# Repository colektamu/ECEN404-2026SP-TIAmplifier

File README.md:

The 2025-2026 TI Amplifier Capstone Project was a senior year capstone project under Texas A&M University and sponsored by Texas Instruments. The project was completed by Haotian Guan, Cole Keating, Braeden Murdock, and Jonathan Roman under the mentorship and supervision of Alex Anderson as a contact with Texas Instruments. The files included in this GitHub repository reflect the progress updates and final version of the project.

Each folder within the repository reflects a single subsystem that contributed to the final project. 
Braeden Murdock integrated pcb power subsystem contains files relevant to the power subsystem that powered the device. 
Cole - Pre and power amp contains the files relevant to the analog subsystem, both the preamp that modulated the signal and the power amp that amplified it into the speaker output. 
Microcontroller - Jonathan Roman contains the pcb and code files for the microcontroller subsystem, used to translate mobile app inputs into potentiometer states on the audio circuits.

All other files found in the repository without a set folder are related documentation such as the Functional System Requirements and Validation Plan.

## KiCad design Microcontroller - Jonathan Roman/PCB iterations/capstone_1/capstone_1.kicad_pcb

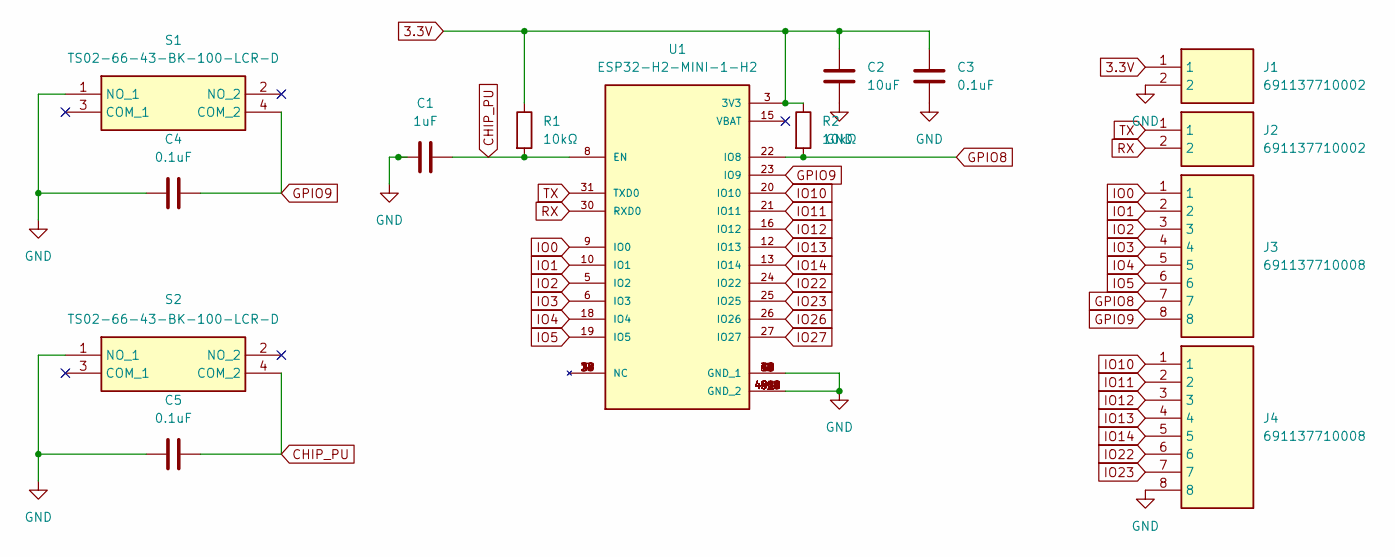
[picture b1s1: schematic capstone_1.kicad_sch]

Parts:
C1: 1uF; C_1206_3216Metric
C2: 10uF; C_1206_3216Metric
C3, C4, C5: 0.1uF; C_1206_3216Metric
J1, J2: 691137710002; SHDR2W70P0X500_1X2_1000X750X1160P; Mouser Part Number 710-691137710002
J3, J4: 691137710008; Mouser Part Number 710-691137710008
R1, R2: 10kΩ; R_1206_3216Metric
S1, S2: TS02-66-43-BK-100-LCR-D; TS026643BK100LCRD; Mouser Part Number 179-TS026643BK100LCR
U1: ESP32-H2-MINI-1-H2; MODULE_ESP32-H2-MINI-1-H2; PARTREV v0.5

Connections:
3.3V: C2.1, C3.1, J1.1, R1.1, R2.1, U1.3 (3V3)
CHIP_PU: C1.1, C5.2, R1.2, S2.4 (COM_2), U1.8 (EN)
GND: C1.2, C2.2, C3.2, C4.1, C5.1, J1.2, J4.8, S1.1 (NO_1), S2.1 (NO_1), U1.1 (GND_1), U1.2 (GND_1), U1.11 (GND_1), U1.14 (GND_1), U1.36 (GND_1), U1.37 (GND_1), U1.38 (GND_1), U1.39 (GND_1), U1.40 (GND_1), U1.41 (GND_1), U1.42 (GND_1), U1.43 (GND_1), U1.44 (GND_1), U1.45 (GND_1), U1.46 (GND_1), U1.47 (GND_2), U1.48 (GND_2), U1.49_1 (GND_2), U1.49_2 (GND_2), U1.49_3 (GND_2), U1.49_4 (GND_2), U1.49_5 (GND_2), U1.49_6 (GND_2), U1.49_7 (GND_2), U1.49_8 (GND_2), U1.49_9 (GND_2), U1.50 (GND_2), U1.51 (GND_2), U1.52 (GND_2), U1.53 (GND_2)
GPIO8: J3.7, R2.2, U1.22 (IO8)
GPIO9: C4.2, J3.8, S1.4 (COM_2), U1.23 (IO9)
IO0: J3.1, U1.9 (IO0)
IO1: J3.2, U1.10 (IO1)
IO2: J3.3, U1.5 (IO2)
IO3: J3.4, U1.6 (IO3)
IO4: J3.5, U1.18 (IO4)
IO5: J3.6, U1.19 (IO5)
IO10: J4.1, U1.20 (IO10)
IO11: J4.2, U1.21 (IO11)
IO12: J4.3, U1.16 (IO12)
IO13: J4.4, U1.12 (IO13)
IO14: J4.5, U1.13 (IO14)
IO22: J4.6, U1.24 (IO22)
IO23: J4.7, U1.25 (IO25)
IO26: U1.26 (IO26)
IO27: U1.27 (IO27)
RX: J2.2, U1.30 (RXD0)
TX: J2.1, U1.31 (TXD0)

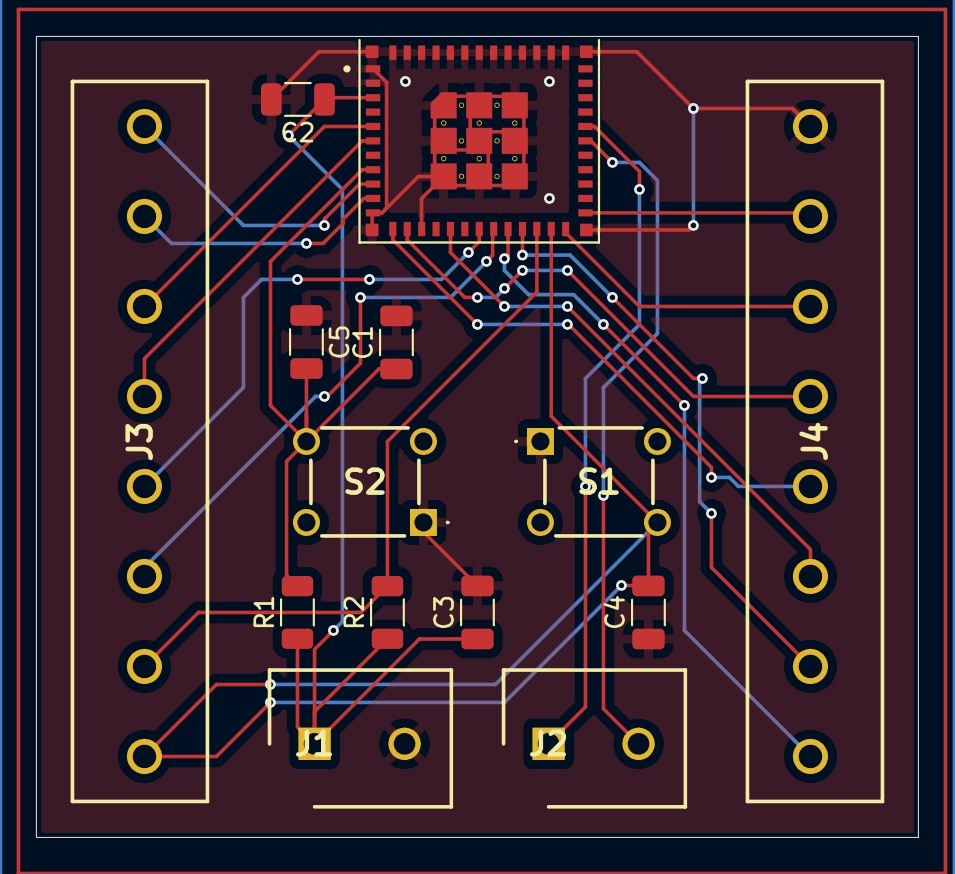
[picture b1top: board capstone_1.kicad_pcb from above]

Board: 2 copper layers, 49.0 x 44.5 mm, 14 parts (0 on the bottom side), 20 nets.

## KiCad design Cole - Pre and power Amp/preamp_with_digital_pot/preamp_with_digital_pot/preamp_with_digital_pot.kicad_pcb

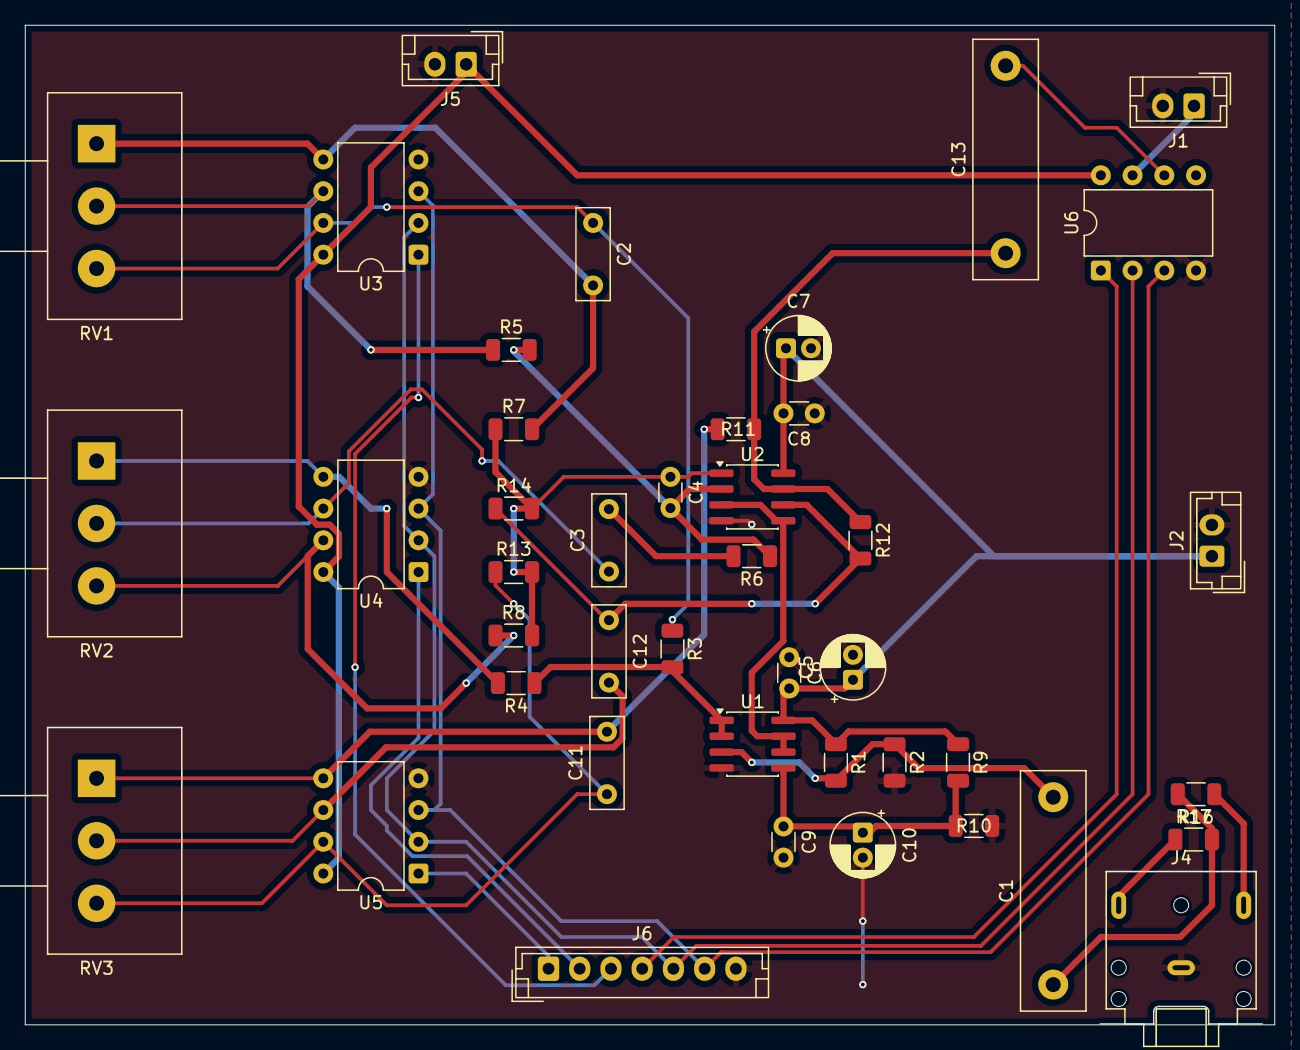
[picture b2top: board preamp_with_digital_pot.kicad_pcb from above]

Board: 2 copper layers, 99.9 x 79.9 mm, 43 parts (0 on the bottom side), 32 nets.

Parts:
C1, C13: 2.2μF; C_Rect_L19.0mm_W5.0mm_P15.00mm_MKS4
C2: 100nF; C_Rect_L7.2mm_W2.5mm_P5.00mm_FKS2_FKP2_MKS2_MKP2
C3: 2.2nF; C_Rect_L7.2mm_W2.5mm_P5.00mm_FKS2_FKP2_MKS2_MKP2
C4: 22pF; C_Disc_D3.0mm_W1.6mm_P2.50mm
C5, C7, C10: 10μF; CP_Radial_D5.0mm_P2.00mm
C6, C8, C9: 0.1μF; C_Disc_D3.0mm_W1.6mm_P2.50mm
C11: 15nF; C_Rect_L7.2mm_W2.5mm_P5.00mm_FKS2_FKP2_MKS2_MKP2
C12: 22nF; C_Rect_L7.2mm_W2.5mm_P5.00mm_FKS2_FKP2_MKS2_MKP2
J1, J2, J5: Conn_01x02; JST_EH_B2B-EH-A_1x02_P2.50mm_Vertical
J4: AudioJack3; Jack_3.5mm_CUI_SJ1-3523N_Horizontal
J6: Conn_01x07; JST_EH_B7B-EH-A_1x07_P2.50mm_Vertical
R1, R2: 100k; R_1206_3216Metric
R3, R7: 5k; R_1206_3216Metric
R4, R8: 2.8k; R_1206_3216Metric
R5: 22k; R_1206_3216Metric
R6: 4.7k; R_1206_3216Metric
R9, R10, R12, R14: 47k; R_1206_3216Metric
R11, R13: 3.6k; R_1206_3216Metric
R16, R17: 2.2k; R_1206_3216Metric
RV1, RV2, RV3: R_Potentiometer; Potentiometer_Alps_RK163_Single_Horizontal
U1, U2: OPA1656ID; SOIC-8_3.9x4.9mm_P1.27mm
U3, U4, U5, U6: MCP4131-xxxx-P; DIP-8_W7.62mm

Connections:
+3.3V: J5.1, U3.8 (V_{DD}), U4.8 (V_{DD}), U5.8 (V_{DD}), U6.8 (V_{DD})
+6V: U1.6 (-), U1.7, U2.3 (+), U2.5 (+)
+12V: C5.1, C6.2, C7.1, C8.2, J2.1, R1.1, R9.1, U1.8 (V+), U2.8 (V+)
CS_BASS: J6.3, U3.1 (~CS)
CS_MID: J6.1, U5.1 (~CS)
CS_TREBLE: J6.2, U4.1 (~CS)
GND: C5.2, C6.1, C7.2, C8.1, C9.2, C10.2, J1.2, J2.2, J4.S, J5.2, J6.7, R2.2, R10.2, U1.4 (V-), U2.4 (V-), U3.4 (V_{SS}), U4.4 (V_{SS}), U5.4 (V_{SS}), U6.4 (V_{SS})
unnamed: C1.1, R16.2, R17.2
unnamed: C3.2, R6.2
unnamed: C4.1, R7.1, R8.2, R13.2, R14.2, U2.1
unnamed: C13.1, R11.2, R12.1, U2.7
unnamed: J1.1, U6.7 (P0B)
unnamed: J4.R, R17.1
unnamed: J4.T, R16.1
unnamed: C1.2, R1.2, R2.1, U1.3 (+)
unnamed: R3.2, R4.1, U1.1, U1.2 (-)
unnamed: C9.1, C10.1, R9.2, R10.1, U1.5 (+)
unnamed: C4.2, R5.2, R6.1, U2.2 (-)
unnamed: C12.1, R12.2, R14.1, U2.6 (-)
unnamed: C2.2, R7.2, RV1.1, U3.5 (P0A)
unnamed: C2.1, R3.1, RV1.3, U3.7 (P0B)
unnamed: R5.1, RV1.2, U3.6 (P0W)
unnamed: R4.2, RV2.1, U4.5 (P0A)
unnamed: R8.1, RV2.3, U4.7 (P0B)
unnamed: C3.1, RV2.2, U4.6 (P0W)
unnamed: C11.2, R11.1, RV3.1, U5.5 (P0A)
unnamed: C11.1, R13.1, RV3.3, U5.7 (P0B)
unnamed: C12.2, RV3.2, U5.6 (P0W)
unnamed: C13.2, U6.6 (P0W)
SCK: J6.5, U3.2 (SCK), U4.2 (SCK), U5.2 (SCK), U6.2 (SCK)
SDI: J6.6, U3.3 (SDI/SDO), U4.3 (SDI/SDO), U5.3 (SDI/SDO), U6.3 (SDI/SDO)
VOL: J6.4, U6.1 (~CS)

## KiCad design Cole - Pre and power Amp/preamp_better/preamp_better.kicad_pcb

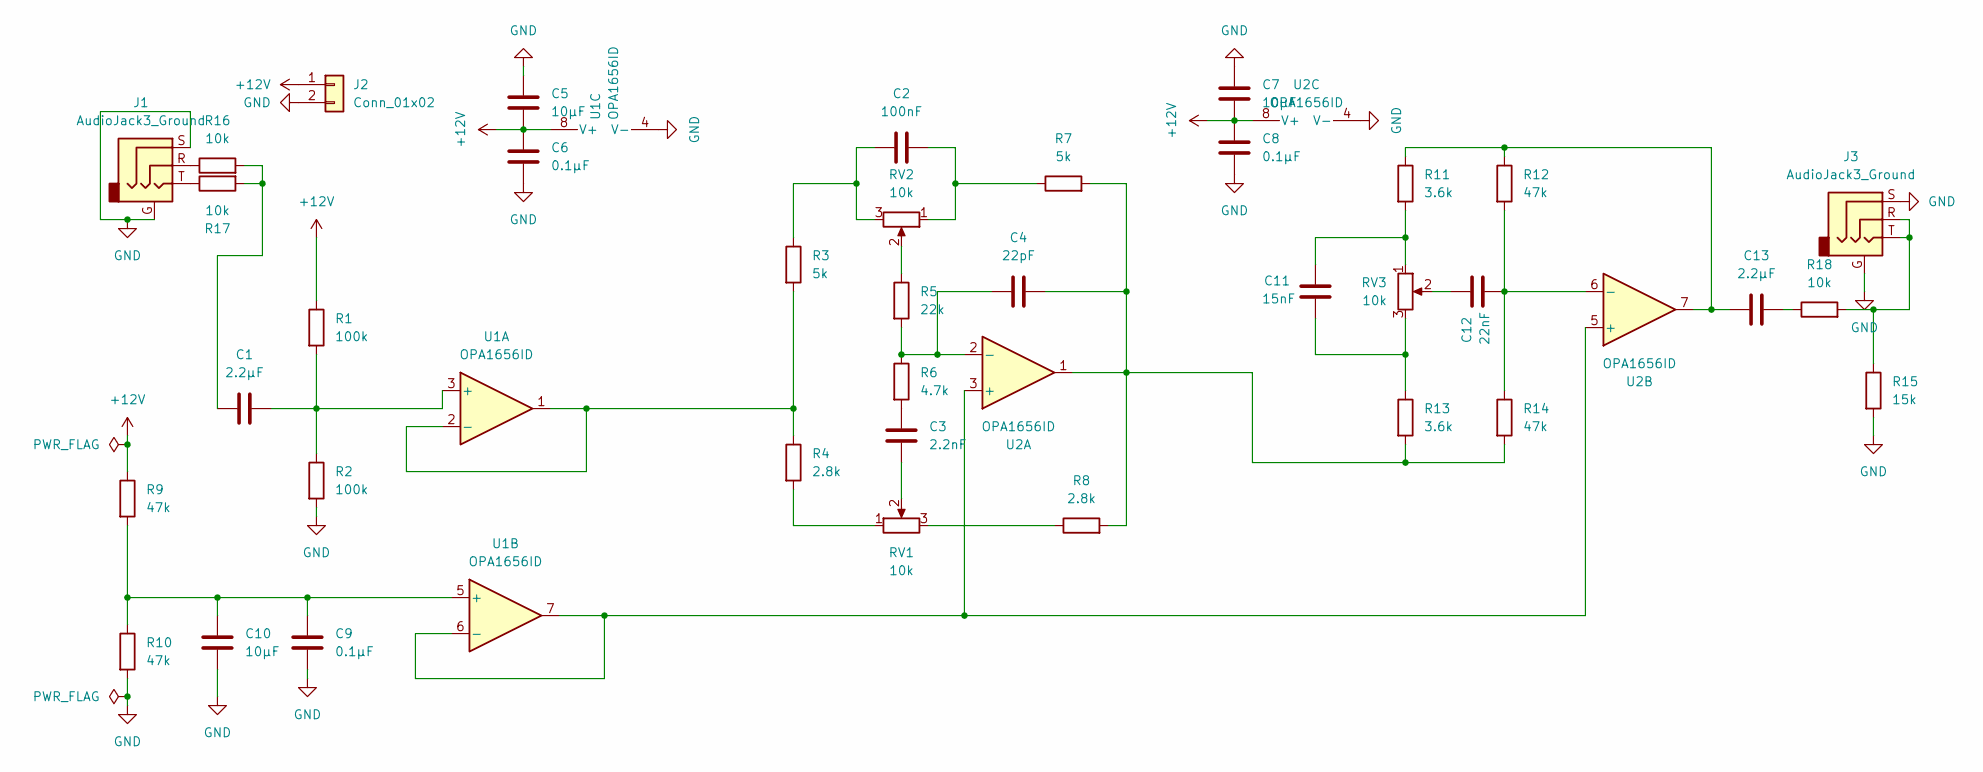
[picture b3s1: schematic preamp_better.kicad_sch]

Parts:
C1, C13: 2.2μF; C_Rect_L19.0mm_W5.0mm_P15.00mm_MKS4
C2: 100nF; C_Rect_L7.2mm_W2.5mm_P5.00mm_FKS2_FKP2_MKS2_MKP2
C3: 2.2nF; C_Rect_L7.2mm_W2.5mm_P5.00mm_FKS2_FKP2_MKS2_MKP2
C4: 22pF; C_Disc_D3.0mm_W1.6mm_P2.50mm
C5, C7, C10: 10μF; CP_Radial_D5.0mm_P2.00mm
C6, C8, C9: 0.1μF; C_Disc_D3.0mm_W1.6mm_P2.50mm
C11: 15nF; C_Rect_L7.2mm_W2.5mm_P5.00mm_FKS2_FKP2_MKS2_MKP2
C12: 22nF; C_Rect_L7.2mm_W2.5mm_P5.00mm_FKS2_FKP2_MKS2_MKP2
J1, J3: AudioJack3_Ground; Jack_3.5mm_CUI_SJ1-3523N_Horizontal
J2: Conn_01x02; 691137710002
R1, R2: 100k; R_1206_3216Metric
R3, R7: 5k; R_1206_3216Metric
R4, R8: 2.8k; R_1206_3216Metric
R5: 22k; R_1206_3216Metric
R6: 4.7k; R_1206_3216Metric
R9, R10, R12, R14: 47k; R_1206_3216Metric
R11, R13: 3.6k; R_1206_3216Metric
R15: 15k; R_1206_3216Metric
R16, R17, R18: 10k; R_1206_3216Metric
RV1, RV2, RV3: 10k; Potentiometer_Alps_RK163_Single_Horizontal
U1, U2: OPA1656ID; SOIC-8_3.9x4.9mm_P1.27mm

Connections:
+12V: C5.1, C6.2, C7.1, C8.2, J2.1, R1.1, R9.1, U1.8 (V+), U2.8 (V+)
GND: C5.2, C6.1, C7.2, C8.1, C9.2, C10.2, J1.G, J1.S, J2.2, J3.G, J3.S, R2.2, R10.2, R15.2, U1.4 (V-), U2.4 (V-)
unnamed: C1.1, R16.2, R17.2
unnamed: C2.1, R3.1, RV2.3
unnamed: C2.2, R7.1, RV2.1
unnamed: C3.1, RV1.2
unnamed: C3.2, R6.2
unnamed: C4.1, R7.2, R8.2, R13.2, R14.2, U2.1
unnamed: C11.1, R13.1, RV3.3
unnamed: C11.2, R11.2, RV3.1
unnamed: C12.2, RV3.2
unnamed: C13.1, R11.1, R12.1, U2.7
unnamed: C13.2, R18.1
unnamed: J1.R, R16.1
unnamed: J1.T, R17.1
unnamed: J3.R, J3.T, R15.1, R18.2
unnamed: R4.2, RV1.1
unnamed: R5.1, RV2.2
unnamed: R8.1, RV1.3
unnamed: C1.2, R1.2, R2.1, U1.3 (+)
unnamed: R3.2, R4.1, U1.1, U1.2 (-)
unnamed: C9.1, C10.1, R9.2, R10.1, U1.5 (+)
unnamed: U1.6 (-), U1.7, U2.3 (+), U2.5 (+)
unnamed: C4.2, R5.2, R6.1, U2.2 (-)
unnamed: C12.1, R12.2, R14.1, U2.6 (-)

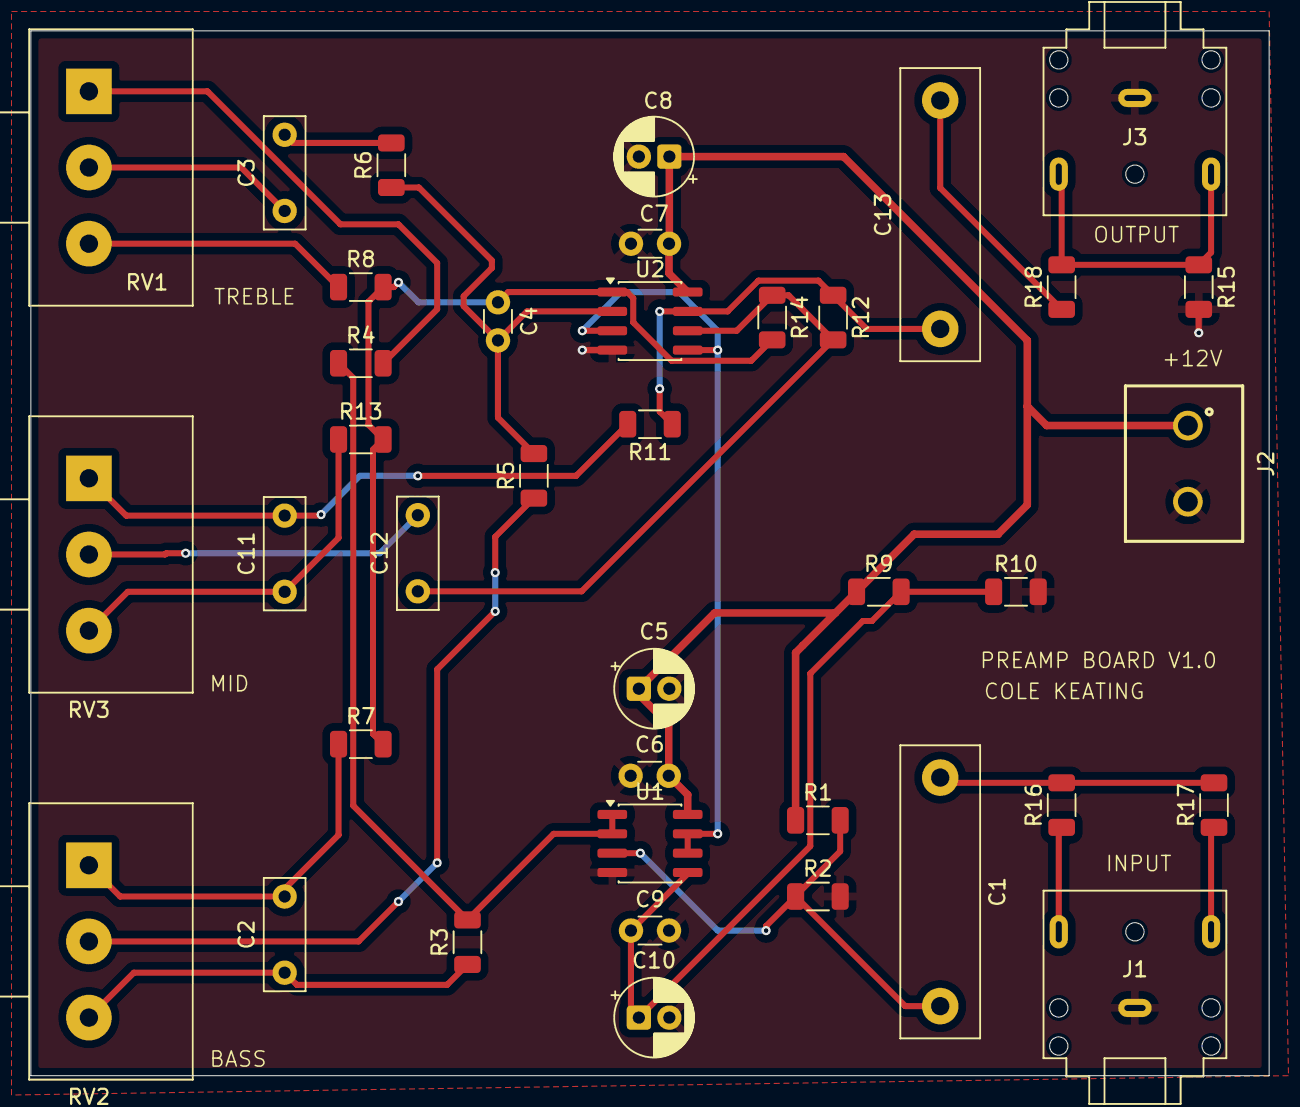
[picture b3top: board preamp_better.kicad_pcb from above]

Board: 2 copper layers, 81.3 x 68.6 mm, 39 parts (0 on the bottom side), 25 nets.

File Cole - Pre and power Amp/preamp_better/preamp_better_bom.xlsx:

Reference | Qty | Value | LINK | Exclude from BOM | Exclude from Board | Footprint | Datasheet
C1,C13 | 2 | 2.2ŒºF |  |  |  | Capacitor_THT:C_Rect_L19.0mm_W5.0mm_P15.00mm_MKS4 | https://www.mouser.com/ProductDetail/871-B32522C225J
C2 | 1 | 100nF |  |  |  | Capacitor_THT:C_Rect_L7.2mm_W2.5mm_P5.00mm_FKS2_FKP2_MKS2_MKP2 | https://www.mouser.com/ProductDetail/Vishay-BC-Components/K1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
C3 | 1 | 2.2nF |  |  |  | Capacitor_THT:C_Rect_L7.2mm_W2.5mm_P5.00mm_FKS2_FKP2_MKS2_MKP2 | https://www.mouser.com/ProductDetail/Vishay-BC-Components/K2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
C4 | 1 | 22pF |  |  |  | Capacitor_THT:C_Disc_D3.0mm_W1.6mm_P2.50mm | https://www.mouser.com/ProductDetail/594-K220J15C0GF5TL2
C5,C7,C10 | 3 | 10ŒºF |  |  |  | Capacitor_THT:CP_Radial_D5.0mm_P2.00mm | https://www.mouser.com/ProductDetail/232-50YXJ10M5X11
C6,C8,C9 | 3 | 0.1ŒºF |  |  |  | Capacitor_THT:C_Disc_D3.0mm_W1.6mm_P2.50mm | https://www.mouser.com/ProductDetail/594-K104K15X7RF5TL2
C11 | 1 | 15nF |  |  |  | Capacitor_THT:C_Rect_L7.2mm_W2.5mm_P5.00mm_FKS2_FKP2_MKS2_MKP2 | https://www.mouser.com/ProductDetail/594-K153K10X7RF5UH5
C12 | 1 | 22nF |  |  |  | Capacitor_THT:C_Rect_L7.2mm_W2.5mm_P5.00mm_FKS2_FKP2_MKS2_MKP2 | https://www.mouser.com/ProductDetail/Vishay-BC-Components/K2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
J1,J3 | 2 | AudioJack3_Ground |  |  |  | Connector_Audio:Jack_3.5mm_CUI_SJ1-3523N_Horizontal | https://www.mouser.com/ProductDetail/490-SJ1-3523N
J2 | 1 | Conn_01x02 |  |  |  | Connector_JST:JST_XH_B2B-XH-A_1x02_P2.50mm_Vertical | https://www.mouser.com/ProductDetail/JST-Commercial/B2B-XH-A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
R1,R2 | 2 | 100k |  |  |  | Resistor_SMD:R_1206_3216Metric | https://www.mouser.com/ProductDetail/603-RC1206FR-07100KL
R3,R7 | 2 | 5k |  |  |  | Resistor_SMD:R_1206_3216Metric | https://www.mouser.com/ProductDetail/603-RC1206FR-074K99L
R4,R8 | 2 | 2.8k |  |  |  | Resistor_SMD:R_1206_3216Metric | https://www.mouser.com/ProductDetail/603-RC1206FR-072K8L
R5 | 1 | 22k |  |  |  | Resistor_SMD:R_1206_3216Metric | https://www.mouser.com/ProductDetail/603-RC1206FR-1022KL
R6 | 1 | 4.7k |  |  |  | Resistor_SMD:R_1206_3216Metric | https://www.mouser.com/ProductDetail/603-RC1206FR-074K7L
R9,R10,R12,R14 | 4 | 47k |  |  |  | Resistor_SMD:R_1206_3216Metric | https://www.mouser.com/ProductDetail/603-RC1206FR-0747KL
R11,R13 | 2 | 3.6k |  |  |  | Resistor_SMD:R_1206_3216Metric | https://www.mouser.com/ProductDetail/YAGEO/RC1206FR-073K6L?q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
R15 | 1 | 15k |  |  |  | Resistor_SMD:R_1206_3216Metric | https://www.mouser.com/ProductDetail/YAGEO/RC1206FR-0715KL?q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
R16,R17,R18 | 3 | 10k |  |  |  | Resistor_SMD:R_1206_3216Metric | https://www.mouser.com/ProductDetail/YAGEO/RC1206FR-0710KL?q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
RV1,RV2,RV3 | 3 | 10k |  |  |  | Potentiometer_THT:Potentiometer_Alps_RK163_Single_Horizontal
U1,U2 | 2 | OPA1656ID |  |  |  | Package_SO:SOIC-8_3.9x4.9mm_P1.27mm | https://www.ti.com/lit/ds/symlink/opa1656.pdf

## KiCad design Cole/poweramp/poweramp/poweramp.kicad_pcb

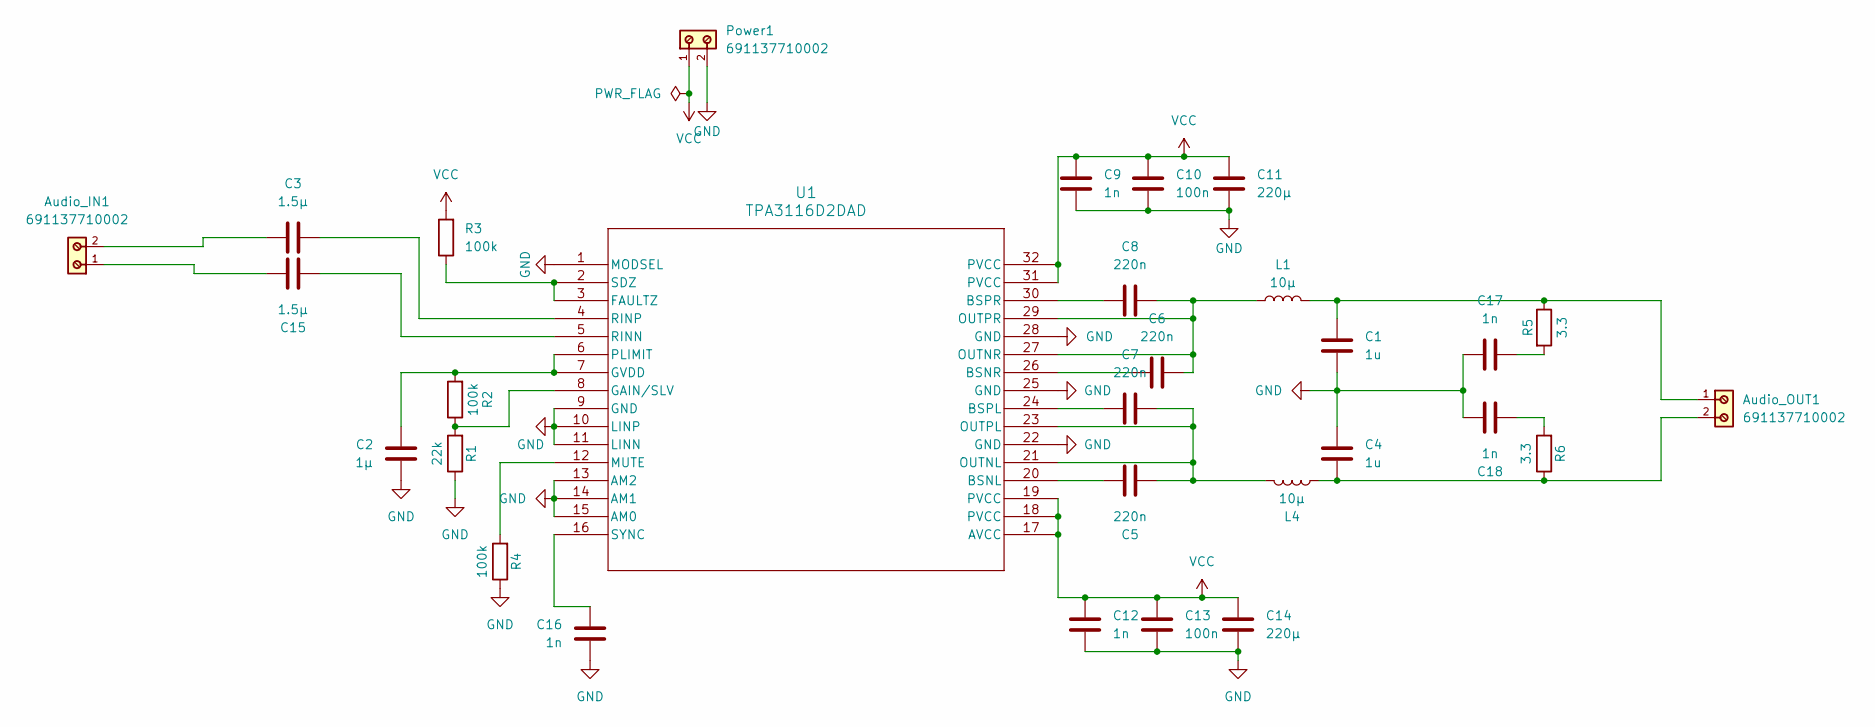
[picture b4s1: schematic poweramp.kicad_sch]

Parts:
Audio_IN1: 691137710002
Audio_OUT1: 691137710002
C1, C4: 1u; C_1206_3216Metric
C2: 1μ; C_1206_3216Metric
C3, C15: 1.5μ; C_Rect_L19.0mm_W5.0mm_P15.00mm_MKS4
C5, C6, C7, C8: 220n; C_1206_3216Metric
C9, C12, C16, C17, C18: 1n; C_1206_3216Metric
C10, C13: 100n; C_1206_3216Metric
C11, C14: 220μ; CP_Radial_D6.3mm_P2.50mm
L1, L4: 10μ; L_TDK_VLS6045EX_VLS6045AF
Power1: 691137710002
R1: 22k; R_Axial_DIN0207_L6.3mm_D2.5mm_P10.16mm_Horizontal
R2: 100k; R_Axial_DIN0207_L6.3mm_D2.5mm_P10.16mm_Horizontal
R3, R4: 100k; R_1206_3216Metric
R5, R6: 3.3; R_Axial_DIN0207_L6.3mm_D2.5mm_P10.16mm_Horizontal
U1: TPA3116D2DAD; DAD32_TEX

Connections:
GND: C1.2, C2.2, C4.2, C9.2, C10.2, C11.2, C12.2, C13.2, C14.2, C16.2, C17.1, C18.1, Power1.2, R1.1, R4.1, U1.1 (MODSEL), U1.9 (GND), U1.10 (LINP), U1.11 (LINN), U1.13 (AM2), U1.14 (AM1), U1.15 (AM0), U1.22 (GND), U1.25 (GND), U1.28 (GND)
unnamed: Audio_IN1.1, C15.1
unnamed: Audio_IN1.2, C3.1
unnamed: Audio_OUT1.1, C1.1, L1.2, R5.1
unnamed: Audio_OUT1.2, C4.1, L4.2, R6.1
unnamed: C17.2, R5.2
unnamed: C18.2, R6.2
unnamed: C5.2, U1.20 (BSNL)
unnamed: C6.2, U1.26 (BSNR)
unnamed: C7.2, U1.24 (BSPL)
unnamed: C8.2, U1.30 (BSPR)
unnamed: R3.1, U1.2 (SDZ), U1.3 (FAULTZ)
unnamed: R1.2, R2.1, U1.8 (GAIN/SLV)
unnamed: C2.1, R2.2, U1.6 (PLIMIT), U1.7 (GVDD)
unnamed: R4.2, U1.12 (MUTE)
unnamed: C5.1, C7.1, L4.1, U1.21 (OUTNL), U1.23 (OUTPL)
unnamed: C6.1, C8.1, L1.1, U1.27 (OUTNR), U1.29 (OUTPR)
unnamed: C15.2, U1.5 (RINN)
unnamed: C3.2, U1.4 (RINP)
unnamed: C16.1, U1.16 (SYNC)
VCC: C9.1, C10.1, C11.1, C12.1, C13.1, C14.1, Power1.1, R3.2, U1.17 (AVCC), U1.18 (PVCC), U1.19 (PVCC), U1.31 (PVCC), U1.32 (PVCC)

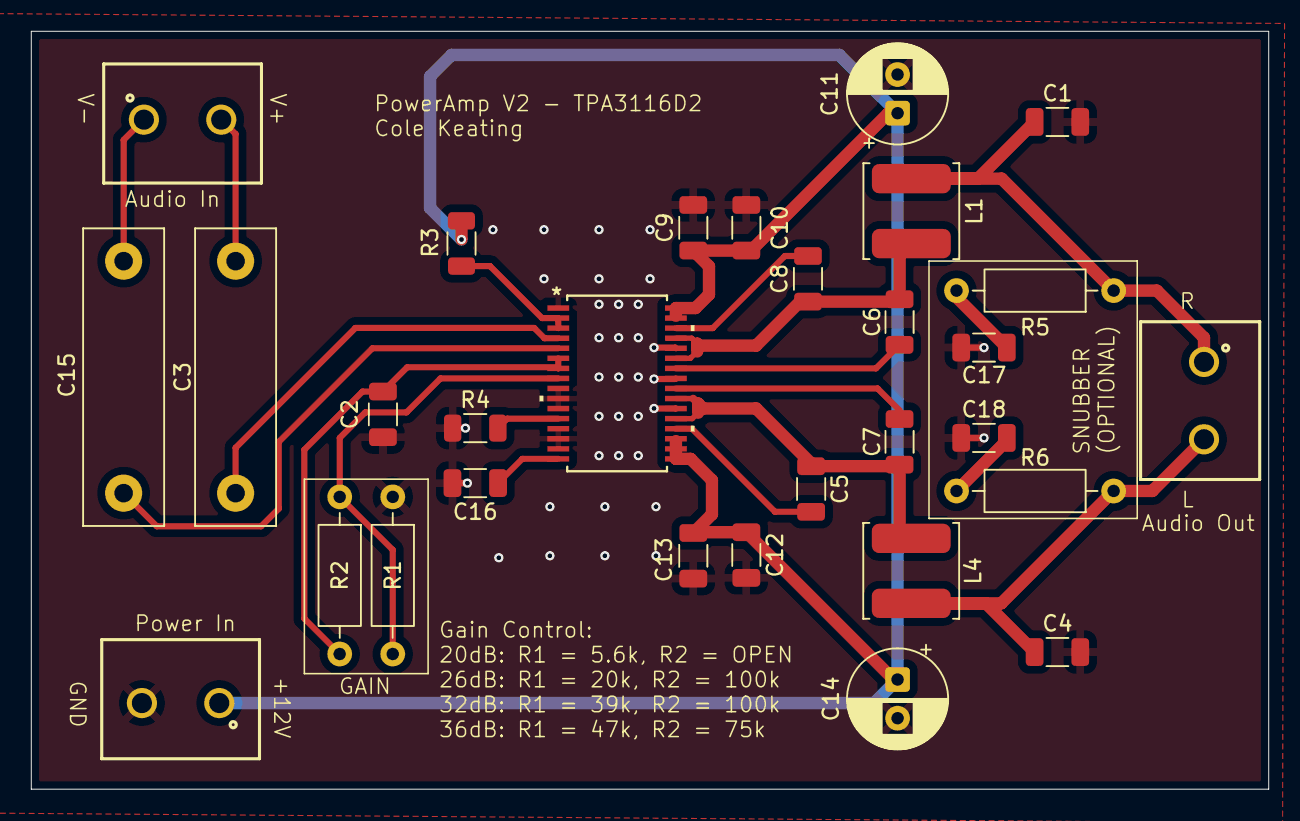
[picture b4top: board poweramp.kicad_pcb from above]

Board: 2 copper layers, 80.0 x 49.0 mm, 30 parts (0 on the bottom side), 21 nets.

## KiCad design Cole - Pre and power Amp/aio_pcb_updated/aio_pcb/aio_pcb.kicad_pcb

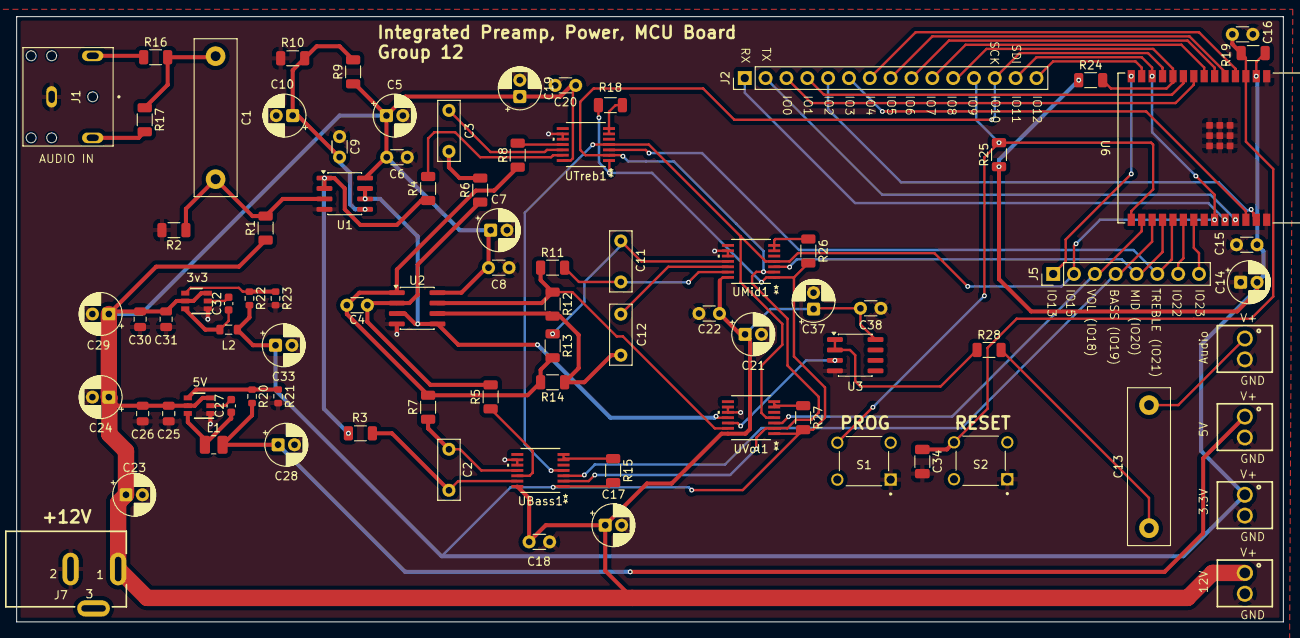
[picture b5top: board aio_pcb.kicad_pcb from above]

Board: 2 copper layers, 154.4 x 73.8 mm, 86 parts (0 on the bottom side), 62 nets.

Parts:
C1, C13: 2.2μF; C_Rect_L19.0mm_W5.0mm_P15.00mm_MKS4
C2: 100nF; C_Rect_L7.2mm_W2.5mm_P5.00mm_FKS2_FKP2_MKS2_MKP2
C3: 2.2nF; C_Rect_L7.2mm_W2.5mm_P5.00mm_FKS2_FKP2_MKS2_MKP2
C4: 22pF; C_Disc_D3.0mm_W1.6mm_P2.50mm
C5, C7, C10, C14, C17, C19, C21, C37: 10μF; CP_Radial_D5.0mm_P2.00mm
C6, C8, C9, C15, C18, C20, C22, C38: 0.1μF; C_Disc_D3.0mm_W1.6mm_P2.50mm
C11: 15nF; C_Rect_L7.2mm_W2.5mm_P5.00mm_FKS2_FKP2_MKS2_MKP2
C12: 22nF; C_Rect_L7.2mm_W2.5mm_P5.00mm_FKS2_FKP2_MKS2_MKP2
C16: 1uF; C_Disc_D3.0mm_W1.6mm_P2.50mm
C23, C24, C28, C29, C33: 47uF; CP_Radial_D5.0mm_P2.00mm
C25, C26, C30, C31: 10uF; C_0805_2012Metric
C27, C32: 100nF; C_0603_1608Metric
C34: 0.1u; C_1206_3216Metric
J1: SJ1-3523N; CUI_SJ1-3523N
J2: Conn_01x15; PinHeader_1x15_P2.54mm_Vertical
J4, J5V1, J33V1: 691210910002
J5: Conn_01x08; PinHeader_1x08_P2.54mm_Vertical
J7: 694108301002
JAUDIO1: 691210910002
L1: 4.7uH; L_1008_2520Metric
L2: 3.3uH; L_0805_2012Metric
R1, R2: 100k; R_1206_3216Metric
R3, R7: 5k; R_1206_3216Metric
R4, R8: 2.8k; R_1206_3216Metric
R5: 22k; R_1206_3216Metric
R6: 4.7k; R_1206_3216Metric
R9, R10, R12, R14: 47k; R_1206_3216Metric
R11, R13: 3.6k; R_1206_3216Metric
R15, R18, R19, R24, R25, R26, R27: 10k; R_1206_3216Metric
R16, R17: 2.2k; R_1206_3216Metric
R20: 56.2k; R_0603_1608Metric
R21, R23: 10k; R_0603_1608Metric
R22: 33.2k; R_0603_1608Metric
R28: 100; R_1206_3216Metric
S1, S2: TS02-66-43-BK-100-LCR-D; SW_TS02-66-43-BK-100-LCR-D
U1, U2, U3: OPA1656ID; SOIC-8_3.9x4.9mm_P1.27mm
U6: ESP32-C6-WROOM-1-N4; MOD28_ESP32-C6-WROOM-1_EXP
UBass1: MCP41HV51-103E/ST; TSSOP14_MC_MCH
UMid1: MCP41HV51-103E/ST; TSSOP14_MC_MCH
UTreb1: MCP41HV51-103E/ST; TSSOP14_MC_MCH
UVol1: MCP41HV51-103E/ST; TSSOP14_MC_MCH
U_5V2, U_33: TPS561201DDCR; DDC0006A_N

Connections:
3.3V: C14.2, C15.2, C33.1, J33V1.1, L2.2, R15.2, R18.2, R19.1, R22.1, R24.1, R25.1, R26.2, R27.2, U6.2 (3V3), UBass1.1 (VL), UMid1.1 (VL), UTreb1.1 (VL), UVol1.1 (VL)
5V: C28.1, J5V1.1, L1.2, R20.1
6V: U1.6 (-), U1.7, U2.3 (+), U2.5 (+), UVol1.11 (P0B)
+12V: C5.1, C6.2, C7.1, C8.2, C17.1, C18.2, C19.1, C20.2, C21.1, C22.2, C23.1, C24.1, C25.1, C26.1, C29.1, C30.1, C31.1, C37.1, C38.2, J4.1, J7.1, R1.1, R9.1, U1.8 (V+), U2.8 (V+), U3.8 (V+), UBass1.14 (V+), UMid1.14 (V+), UTreb1.14 (V+), UVol1.14 (V+), U_5V2.3 (VIN), U_5V2.5 (EN), U_33.3 (VIN), U_33.5 (EN)
Bass_CS: J5.4, U6.17 (IO19), UBass1.3 (*CS)
GND: C5.2, C6.1, C7.2, C8.1, C9.2, C10.2, C14.1, C15.1, C16.1, C17.2, C18.1, C19.2, C20.1, C21.2, C22.1, C23.2, C24.2, C25.2, C26.2, C28.2, C29.2, C30.2, C31.2, C33.2, C34.2, C37.2, C38.1, J1.1, J4.2, J5V1.2, J7.2, J33V1.2, JAUDIO1.2, R2.2, R10.2, R21.2, R23.2, S1.1, S2.1, U1.4 (V-), U2.4 (V-), U3.4 (V-), U6.1 (GND), U6.28 (GND), U6.29 (GND), U6.30 (GND), U6.31 (GND), U6.32 (GND), U6.33 (GND), U6.34 (GND), U6.35 (GND), U6.36 (GND), U6.37 (GND), UBass1.9 (DGND), UBass1.10 (V-), UMid1.9 (DGND), UMid1.10 (V-), UTreb1.9 (DGND), UTreb1.10 (V-), UVol1.9 (DGND), UVol1.10 (V-), U_5V2.1 (GND), U_33.1 (GND)
IO0: J2.3, U6.8 (IO0)
IO1: J2.4, U6.9 (IO1)
IO2: J2.5, U6.27 (IO2)
IO3: J2.6, U6.26 (IO3)
IO4: J2.7, U6.4 (IO4)
IO5: J2.8, U6.5 (IO5)
IO6: J2.9, U6.6 (IO6)
IO7: J2.10, U6.7 (IO7)
IO8: J2.11, R24.2, U6.10 (IO8)
IO9: J2.12, R25.2, S1.4, U6.15 (IO9)
IO10: J2.13, U6.11 (IO10), UBass1.2 (SCK), UMid1.2 (SCK), UTreb1.2 (SCK), UVol1.2 (SCK)
IO11: J2.14, J5.2, U6.12 (IO11), U6.23 (IO15), UBass1.4 (SDI), UMid1.4 (SDI), UTreb1.4 (SDI), UVol1.4 (SDI)
IO12: J2.15, U6.13 (IO12)
IO13: J5.1, U6.14 (IO13)
IO18: J5.3, U6.16 (IO18), UVol1.3 (*CS)
IO20: J5.5, U6.18 (IO20), UMid1.3 (*CS)
IO21: J5.6, U6.19 (IO21), UTreb1.3 (*CS)
IO22: J5.7, U6.20 (IO22)
IO23: J5.8, U6.21 (IO23)
unnamed: C1.1, R16.2, R17.1
unnamed: C3.2, R6.2
unnamed: C4.1, R7.2, R8.2, R13.2, R14.2, U2.1
unnamed: C13.1, R28.2
unnamed: C13.2, JAUDIO1.1
unnamed: J1.2, R17.2
unnamed: J1.3, R16.1
unnamed: C1.2, R1.2, R2.1, U1.3 (+)
unnamed: R3.2, R4.1, U1.1, U1.2 (-)
unnamed: C9.1, C10.1, R9.2, R10.1, U1.5 (+)
unnamed: C4.2, R5.2, R6.1, U2.2 (-)
unnamed: C12.1, R12.2, R14.1, U2.6 (-)
unnamed: R28.1, U3.1, U3.2 (-)
unnamed: R15.1, UBass1.6 (*WLAT), UBass1.7 (*SHDN)
unnamed: R26.1, UMid1.6 (*WLAT), UMid1.7 (*SHDN)
unnamed: R18.1, UTreb1.6 (*WLAT), UTreb1.7 (*SHDN)
unnamed: R27.1, UVol1.6 (*WLAT), UVol1.7 (*SHDN)
unnamed: C27.2, U_5V2.2 (SW)
unnamed: C27.1, L1.1, U_5V2.6 (VBST)
unnamed: R20.2, R21.1, U_5V2.4 (VFB)
unnamed: C32.2, U_33.2 (SW)
unnamed: C32.1, L2.1, U_33.6 (VBST)
unnamed: R22.2, R23.1, U_33.4 (VFB)
RX: J2.1, U6.24 (RXD0)
TX: J2.2, U6.25 (TXD0)
aud_a: R11.1, R12.1, U2.7, UVol1.13 (P0A)
aud_w: U3.3 (+), UVol1.12 (P0W)
bass_a: C2.1, R3.1, UBass1.13 (P0A)
bass_b: C2.2, R7.1, UBass1.11 (P0B)
bass_w: R5.1, UBass1.12 (P0W)
mid_a: C11.2, R11.2, UMid1.13 (P0A)
mid_b: C11.1, R13.1, UMid1.11 (P0B)
mid_w: C12.2, UMid1.12 (P0W)
reset: C16.2, C34.1, R19.2, S2.4, U6.3 (EN)
treble_a: R4.2, UTreb1.13 (P0A)
treble_b: R8.1, UTreb1.11 (P0B)
treble_w: C3.1, UTreb1.12 (P0W)

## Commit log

2026-04-20 initial commit
    Cole's Files
2026-04-20 add mobile app files
2026-04-20 Mobile App by Haotian Guan
2026-04-20 renamed folder
    included info about my subsystems
2026-04-24 files
    all files
2026-04-27 README.md
